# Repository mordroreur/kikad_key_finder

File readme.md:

# Key-Finder design

Ce repository représente le travail de Laurencot Mathieu pour les cinquième, sixième et septième séances du cours "Design à deux balles" animé par M. Marchand et M. Petit.

L'objectif de ce cours était de concevoir un objet concurrent du [mini traceur gps de action](https://www.action.com/fr-fr/p/2579654/mini-traceur-gps/). Pour ce faire, nous avons travaillé sur la carte électronique qui pourrait être intégrée dans le Key-Finder, ainsi que sur le design de l'objet.

Vous trouverez tous les fichiers de mon travail dans ce repository.

## Information

Le travail a été réalisé en utilisant les logiciels KiCad 7.0 et Fusion 360. Il vous suffit de cloner le projet, puis de l'ouvrir avec le logiciel KiCad. Importez ensuite le fichier Design_key_finder.f3z dans l'application Fusion 360.

L'objectif était de partir d'une base du composant nRF52 et d'y ajouter les fonctionnalités que nous avons observées sur le Key-Finder de Action au cours des sessions précédentes.

### Les fonctionnalités standard

La liste des fonctionnalité est disponnible sur le schéma ci-dessous

Pour récapituler le schéma, nous avons ajouté un buzzer relié à la pin 06 de la puce, une LED verte reliée à la pin 09, et un bouton relié à la pin 04. Il y a également le bouton reset, relié à la pin 21 également nommée pin de reset, et une batterie reliée au VCC et à la masse (ground). Enfin, il y a un connecteur de programmation (qui pourrait disparaître dans la version finale) relié aux pins SWDIO, SWDCLK, la pin de reset (inversée) et les pins 22, 23 et 24.

### Le petit plus

De plus, j'ai fait le choix d'ajouter, comme vous pouvez le voir sur le schéma ci-dessus, un microphone relié à la pin 10. C'est une fonctionnalité annoncée sur l'emballage du Key-Finder de Action mais qui n'est pas présente sur la carte électronique, et qui n'existe donc pas. J'ai donc décidé d'ajouter un microphone qui pourrait assez facilement avoir les fonctions suivantes:

- Sonner à une commande vocale précise (pour éviter à l'utilisateur de devoir chercher son téléphone pour ensuite chercher ses clés).
- Pouvoir configurer la commande vocale nécessaire pour sonner (pour éviter d'utiliser un mot anglais assez rare en France, donc qui n'active jamais le Key-Finder sans raison, mais qui, si l'on part en voyage à l'étranger, se retrouve à s'activer fréquemment sans raison).
- Utiliser une commande vocale pour envoyer une commande au téléphone, par exemple, déclencher la prise d'une photo.

### Le designe

Étant donné que c'est mon premier projet sur Fusion, vous remarquerez que les formes sont assez basiques, mais néanmoins efficaces. Le design suit le modèle du Key-Finder de Action, donc on retrouve une boucle pratique pour attacher le Key-Finder à un porte-clés, par exemple, un bouton pour allumer et éteindre l'objet, ou encore pour demander à l'objet d'envoyer un signal au téléphone. Il y a aussi un capuchon qui protège la pile (facilement amovible, ce qui permet de changer la pile au besoin) et enfin un trou traversant en face de la LED pour voir quand la LED s'allume des deux côtés de l'objet.

De plus, contrairement à l'objet d'Action, j'ai choisi d'augmenter la portée du son du buzzer en ne bloquant pas le son. Pour ce faire, j'ai créé quelques ouvertures sur les coques. Un groupe de sorties est situé au-dessus du buzzer, et un groupe est situé en dessous du microphone.
L'inconvénient de ce choix est la perte de la résistance à l'eau, mais étant donné qu'il n'y a aucun joint sur l'objet original et qu'il y a un trou pour la lumière de la LED, je ne pense pas avoir beaucoup détérioré cet aspect.

## Limitation

### Electronique

Au cours de ce travail, je me suis heurté à de nombreux problèmes électroniques, dont certains ne sont actuellement pas résolus, ce qui fait que dans l'état actuel, la carte n'est pas utilisable. On peut notamment citer le fait que la pin reset du JTAG est censée être inversée, mais ne connaissant pas les inverseurs, je n'ai pas pu le faire.
On peut également mentionner les traces lors du tracé qui ont quelques angles un peu aigus, ce qui risquerait de créer des résonances et donc de poser des problèmes avec la norme CE. De plus, l'antenne n'est certainement pas réalisée exactement au centième de millimètre près.
Enfin, certains des composants sont probablement mal câblés en raison de mon manque de connaissance dans ce domaine en particulier.

### Designe

Pour la partie design, pas trop de problème, il faudrait juste, pour améliorer le design, avoir des connaissances en physique supplémentaires pour connaître la taille minimale d'un trou qui peut permettre à l'eau de s'infiltrer ou encore la disposition adéquate pour que des trous laissent passer le son le mieux possible. De plus, il est possible que le design manque de calles en haut et en bas pour bloquer le PCB, mais comme le PCB est censé s'emboîter parfaitement, il ne devrait pas bouger, c'est à mon avis un test à réaliser.

## Conclusion

Ce repository est la conclusion d'un semestre de travail sur un Key-Finder. Ce travail pourrait être amélioré par des connaissances en physique plus approfondies. Ou encore des tests avec des objets physiques, mais le résultat de ce travail est globalement presque réalisable, il ne resterait plus qu'à y intégrer le code.

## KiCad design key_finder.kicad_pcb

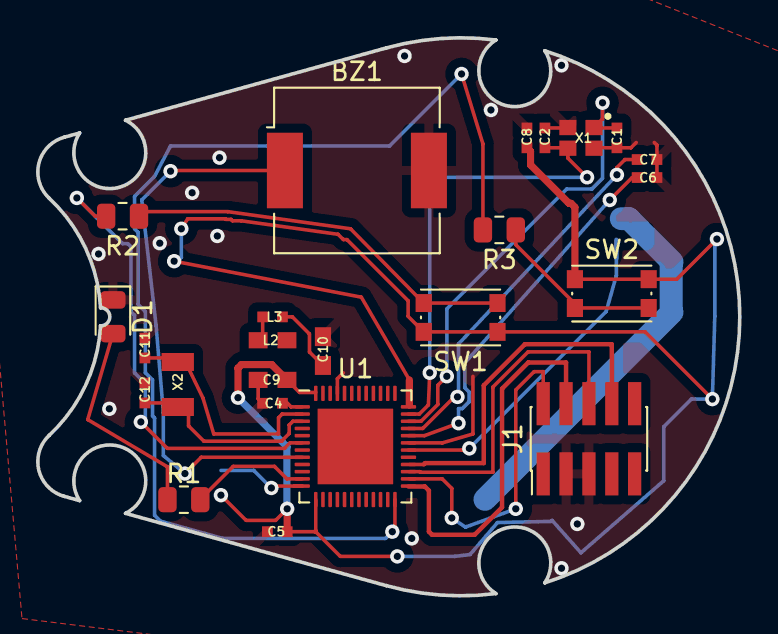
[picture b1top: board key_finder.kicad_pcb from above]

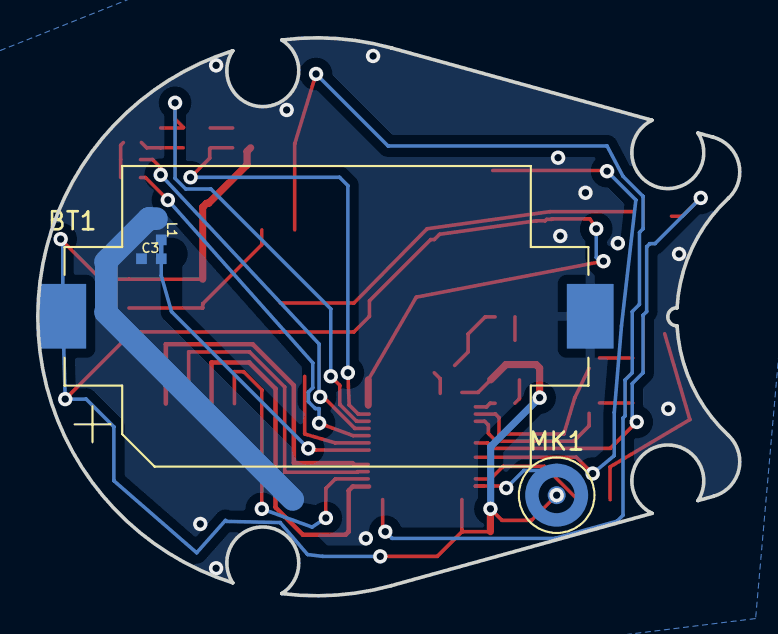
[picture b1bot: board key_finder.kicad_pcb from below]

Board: 2 copper layers, 39.0 x 31.0 mm, 28 parts (4 on the bottom side), 23 nets.

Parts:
BT1: Battery; BatteryHolder_Keystone_1060_1x2032
BZ1: Buzzer; Buzzer_CUI_CPT-9019S-SMT
C1, C2, C11, C12: 12pF; RESC0402_N
C3: 0.8pF; RESC0402_N
C4, C5, C8: 100nF; RESC0402_N
C6: N.M.; RESC0402_N
C7: 100pF; RESC0402_N
C9: 4.7µF; RESC0603_N
C10: 1.0µF; RESC0603_N
D1: LED; LED_0805_2012Metric
J1: Conn_ARM_JTAG_SWD_10; PinHeader_2x05_P1.27mm_Vertical_SMD
L1: 3.9nH; RESC0402_N
L2: 10µH; RESC0603_N
L3: 15nH; RESC0402_N
MK1: Microphone; CUI_CMC-4013-SMT
R1: 330; R_0805_2012Metric
R2, R3: 10k; R_0805_2012Metric
SW1, SW2: SW_Push; SW_Push_1P1T_NO_CK_KMR2
U1: NRF52832; QFN-48-1EP_6x6mm_P0.4mm_EP4.2x4.2mm
X1: 32MHz; BT-XTAL_2016_N
X2: 32.768kHz; XTAL_3215_N

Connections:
/DEC2: C6.1, U1.32 (DEC2@32)
/DEC3: C7.1, U1.33 (DEC3@33)
/P0.04: R2.2, U1.6 (P0.04/AIN2@06)
/P0.06: BZ1.1 (-), U1.8 (P0.06@08)
/P0.09: R1.2, U1.11 (P0.09/NFC1@11)
/P0.10: MK1.1 (-), U1.12 (P0.10/NFC2@12)
/P0.21/RESET: R3.2, U1.24 (P0.21/RESET@24)
/P0.22: J1.6 (SWO/TDO), U1.27 (P0.22@27)
/P0.23: J1.8 (NC/TDI), U1.28 (P0.23@28)
/SWDCLK: J1.4 (SWDCLK/TCK), U1.25 (SWDCLK@25)
/SWDIO: J1.2 (SWDIO/TMS), U1.26 (SWDIO@26)
DEC4: C10.1, L3.2
GND: BT1.2 (-), BZ1.2 (+), C1.2, C2.2, C3.2, C4.2, C5.2, C6.2, C7.2, C8.2, C9.2, C10.2, C11.1, C12.1, D1.1 (K), J1.3 (GND), J1.5 (GND), U1.31 (VSS@31), U1.45 (VSS@45), X1.2, X1.4
unnamed: L2.2, L3.1
unnamed: D1.2 (A), R1.1
unnamed: R2.1, SW1.2
unnamed: R3.1, SW2.2
unnamed: C3.1, L1.1, U1.30 (ANT@30)
unnamed: C1.1, U1.34 (XC1@34), X1.1
unnamed: C2.1, U1.35 (XC2@35), X1.3
P0.00/XL1: C11.2, X2.1
P0.01/XL2: C12.2, X2.2
VCC: BT1.1 (+), C5.1, C8.1, C9.1, MK1.2 (+), SW1.1, SW2.1, U1.13 (VDD@13), U1.36 (VDD@36), U1.48 (VDD@48)

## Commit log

2023-11-20 end of shematic
2023-11-24 change battery + relier les composants
2023-11-26 correct som ref and add readme
2023-11-26 correct sceance number
2023-12-04 sceance 2
2023-12-08 add designe file
2023-12-09 start readme
2023-12-10 correct some details
2023-12-10 add readme informations
2023-12-10 correction readme
